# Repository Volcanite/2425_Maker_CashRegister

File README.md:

# 2425_Maker_CashRegister
Caisse enregistreuse à destination de la KFET. Elle permettrai de payer ses consommations et d'en avoir une traçabilité. On aurait également la possibilité de gérer les stocks et prévenir en cas de rupture. On pourrait également modifier les prix et les consommables proposés.

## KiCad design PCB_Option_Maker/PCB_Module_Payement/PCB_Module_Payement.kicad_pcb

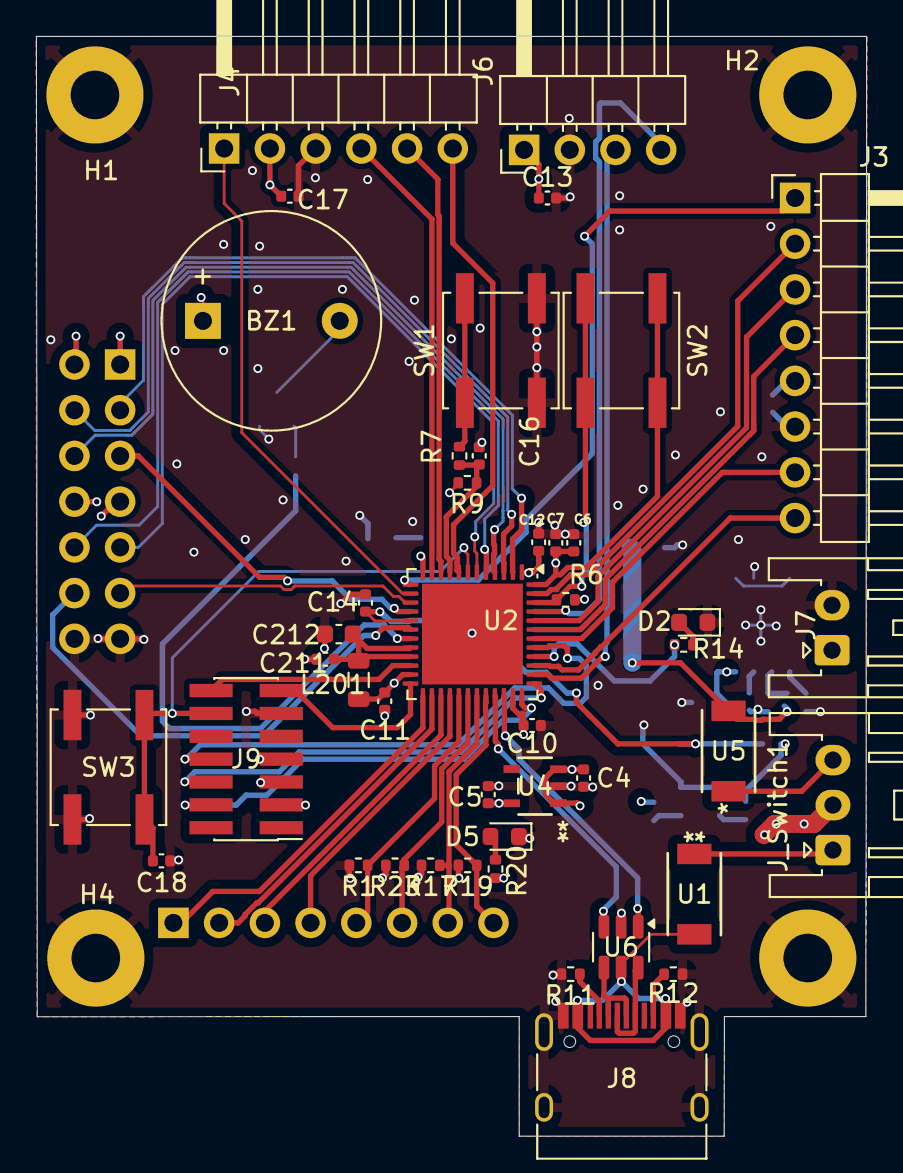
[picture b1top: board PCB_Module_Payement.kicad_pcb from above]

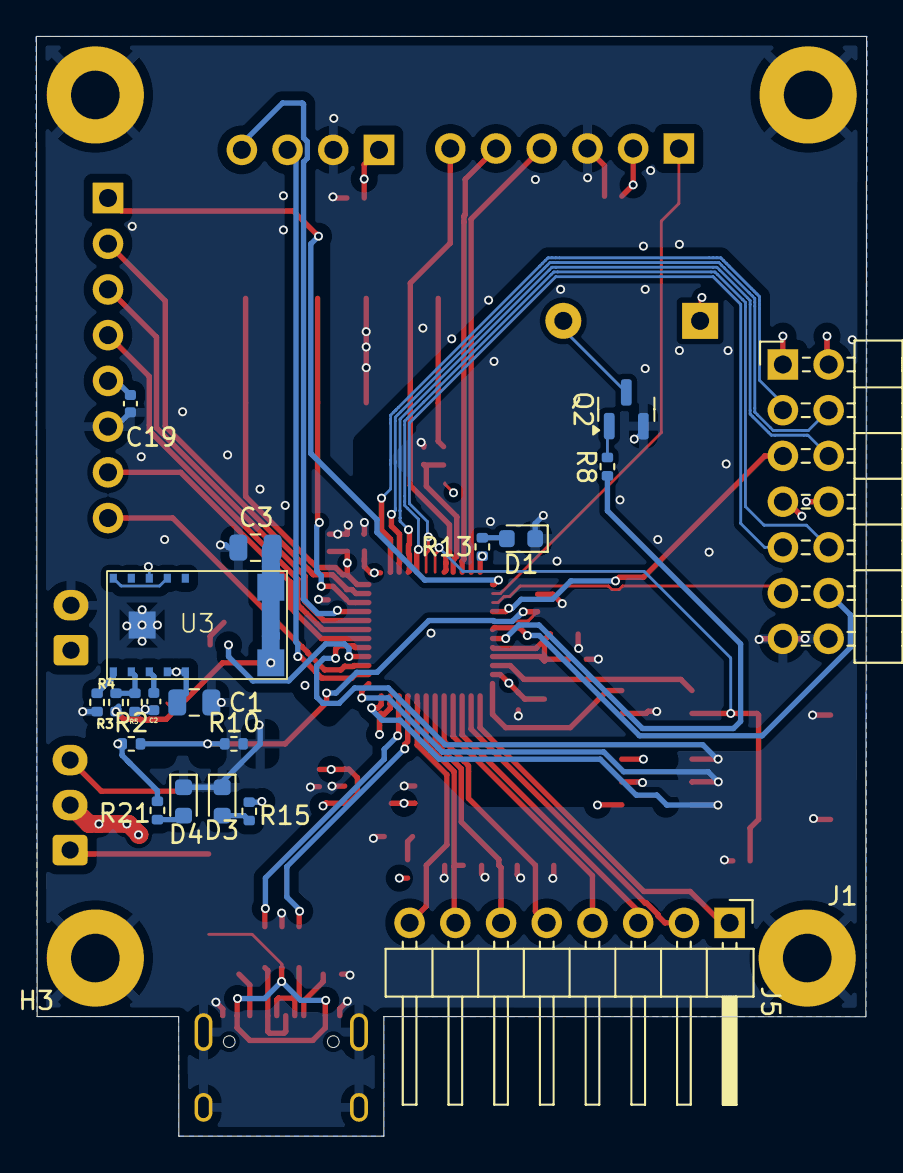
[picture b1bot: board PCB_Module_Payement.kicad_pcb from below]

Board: 4 copper layers, 46.1 x 61.1 mm, 68 parts (20 on the bottom side), 67 nets.

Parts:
BZ1: Buzzer; Buzzer_12x9.5RM7.6
C1: 10u; C_0805_2012Metric
C2, C4, C5, C13, C17, C19: 1u; C_0402_1005Metric
C3: 47u; C_0805_2012Metric
C6: 4u7; C_0402_1005Metric
C7, C10, C11, C12, C14, C16, C18, C211: 100n; C_0402_1005Metric
C212: 1u; C_0603_1608Metric
D1: LED Blue; LED_0603_1608Metric
D2: LED Amber; LED_0603_1608Metric
D3: LED Yellow; LED_0603_1608Metric
D4: LED_Blue; LED_0603_1608Metric
D5: LED_Green; LED_0603_1608Metric
H1, H2, H3, H4: MountingHole_Pad; MountingHole_2.7mm_M2.5_Pad
J1: Conn_02x07_Odd_Even; PinHeader_2x07_P2.54mm_Horizontal
J3, J5: Conn_01x08; PinHeader_1x08_P2.54mm_Horizontal
J4: Conn_01x06; PinHeader_1x06_P2.54mm_Horizontal
J6: Conn_01x04; PinHeader_1x04_P2.54mm_Horizontal
J7: Conn_01x02; JST_XA_S02B-XASK-1_1x02_P2.50mm_Horizontal
J8: USB_C_Receptacle_USB2.0; USB_C_Receptacle_HRO_TYPE-C-31-M-12
J9: Conn_ST_STDC14; PinHeader_2x07_P1.27mm_Vertical_SMD
J_Switch1: Conn_01x03; JST_XA_S03B-XASK-1_1x03_P2.50mm_Horizontal
L201: 39n; L_0805_2012Metric
Q2: MMBT2222A; SOT-23
R1, R17, R19, R23: 10K; R_0402_1005Metric
R2: 168K; R_0402_1005Metric
R3: 5k6; R_0402_1005Metric
R4: 49k9; R_0402_1005Metric
R5, R6, R7, R9: 10k; R_0402_1005Metric
R8: 1K; R_0402_1005Metric
R10: 68K; R_0402_1005Metric
R11, R12: 5.1K; R_0402_1005Metric
R13, R14, R15: 1k7; R_0402_1005Metric
R20: 510; R_0402_1005Metric
R21: R; R_0402_1005Metric
SW1, SW2, SW3: SW_Push; SW_Push_1P1T_NO_CK_KSC6xxJ
U1, U5: FSV330AF; DO-214AD_ONS
U2: STM32G431CBUx; QFN-48-1EP_7x7mm_P0.5mm_EP5.6x5.6mm
U3: 171013801; Wurth_171013801
U4: BU33SD5WG-TR; SSOP5_ROM
U6: USBLC6-2SC6; SOT-23-6

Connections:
5V_BUCK: C3.1, R4.1, U3.6 (Vout), U3.7 (Vout), U5.2 (A)
5V_USB: J8.A4 (VBUS), J8.A9 (VBUS), J8.B4 (VBUS), J8.B9 (VBUS), U1.2 (A), U6.5 (VBUS)
+3.3V: C5.2, C6.1, C7.1, C10.1, C11.1, C12.1, J1.7, J1.8, J9.3 (VCC), L201.1, R9.2, R20.1, SW2.2, U2.1 (VBAT), U2.23 (VDD), U2.35 (VDD), U2.48 (VDD), U4.5 (VOUT)
+3.3VA: C211.1, C212.1, L201.2, U2.20 (VREF+), U2.21 (VDDA)
+5V: BZ1.1 (+), C4.1, C13.1, C17.1, C19.1, J1.1, J1.2, J3.5, J4.2, J6.1, J_Switch1.2, R15.1, U4.1 (VIN), U4.3 (STBY)
/Alim/Charge_Batterie: C14.1, R2.2, R10.1, U2.17 (PB0)
/Modules/Bt_RXD: J4.5, U2.10 (PA2)
/Modules/Bt_TXD: J4.4, U2.11 (PA3)
/Modules/Culomn1: J5.5, R1.1, U2.29 (PC6)
/Modules/Culomn2: J5.6, R23.1, U2.30 (PA8)
/Modules/Culomn3: J5.7, R17.1, U2.31 (PA9)
/Modules/Culomn4: J5.8, R19.1, U2.32 (PA10)
/Modules/I2C1_SCL: J6.4, U2.45 (PB7)
/Modules/I2C1_SDA: J6.3, U2.38 (PA15)
/Modules/IRQ: J3.8, U2.39 (PC10)
/Modules/KEY: J4.6, U2.8 (PA0)
/Modules/R0W1: J5.1, U2.25 (PB12)
/Modules/ROW2: J5.2, U2.26 (PB13)
/Modules/ROW3: J5.3, U2.27 (PB14)
/Modules/ROW4: J5.4, U2.28 (PB15)
/Modules/RSTO: J3.2, U2.47 (PB9)
/Modules/SPI1_Miso: J3.7, U2.42 (PB4)
/Modules/SPI1_Mosi: J3.4, U2.43 (PB5)
/Modules/SPI1_SCK: J3.1, U2.13 (PA5)
/Modules/SS: J3.3, U2.44 (PB6)
/Modules/STATE: J4.1, U2.14 (PA6)
/STM32/BL_LED: R13.1, U2.12 (PA4)
/STM32/BOOT0: R6.1, SW2.1, U2.46 (PB8)
/STM32/BUZZER: R8.1, U2.19 (PB2)
/STM32/Bt_Button: C16.1, R7.2, R9.1, U2.9 (PA1)
/STM32/D+: J8.A6 (D+), J8.B6 (D+), U6.6 (I/O1)
/STM32/D-: J8.A7 (D-), J8.B7 (D-), U6.4 (I/O2)
/STM32/NRST: C18.2, J9.12 (~RST), SW3.2, U2.7 (PG10)
/STM32/PA7: J1.11, U2.15 (PA7)
/STM32/PC4: J1.5, U2.16 (PC4)
/STM32/PC13: J1.3, U2.2 (PC13)
/STM32/PC14: J1.4, U2.3 (PC14)
/STM32/PC15: J1.6, U2.4 (PC15)
/STM32/PF0: J1.10, U2.5 (PF0)
/STM32/PF1: J1.9, U2.6 (PF1)
/STM32/Pb1: J1.12, U2.18 (PB1)
/STM32/RFID_LED: R14.1, U2.40 (PC11)
/STM32/SWCLK: J9.6 (JCLK/SWCLK), U2.37 (PA14)
/STM32/SWDIO: J9.4 (JTMS/SWDIO), U2.36 (PA13)
/STM32/SWO: J9.8 (JTDO/SWO), U2.41 (PB3)
/STM32/USART3_RX: J9.14 (VCP_TX), U2.22 (PB10)
/STM32/USART3_TX: J9.13 (VCP_RX), U2.24 (PB11)
/STM32/USB_D+: U2.34 (PA12), U6.1 (I/O1)
/STM32/USB_D-: U2.33 (PA11), U6.3 (I/O2)
GND: C1.2, C2.2, C3.2, C4.2, C5.1, C6.2, C7.2, C10.2, C11.2, C12.2, C13.2, C14.2, C16.2, C17.2, C18.1, C19.2, C211.2, C212.2, D1.1 (K), D2.1 (K), D3.1 (K), D4.1 (K), D5.1 (K), H1.1, H2.1, H3.1, H4.1, J1.13, J1.14, J3.6, J4.3, J6.2, J7.2, J8.A1 (GND), J8.A12 (GND), J8.B1 (GND), J8.B12 (GND), J8.S1 (SHIELD), J9.5 (GND), J9.7 (GND), J9.11 (GNDDetect), Q2.2 (E), R1.2, R3.2, R5.2, R6.2, R10.2, R11.2, R12.2, R17.2, R19.2, R23.2, SW1.1, SW3.1, U2.49 (VSS), U3.10 (AGND), U3.13 (PGND), U4.2 (GND), U6.2 (GND)
unnamed: BZ1.2 (-), Q2.3 (C)
unnamed: D1.2 (A), R13.2
unnamed: D2.2 (A), R14.2
unnamed: D3.2 (A), R15.2
unnamed: D4.2 (A), R21.2
unnamed: D5.2 (A), R20.2
unnamed: J8.A5 (CC1), R11.1
unnamed: J8.B5 (CC2), R12.1
unnamed: J_Switch1.1, U1.1 (K)
unnamed: J_Switch1.3, U5.1 (K)
unnamed: Q2.1 (B), R8.2
unnamed: R7.1, SW1.2
unnamed: U3.9 (VIN), U3.12 (EN)
unnamed: R4.2, R5.1, U3.2 (FB)
unnamed: R3.1, U3.1 (FSW_1)
unnamed: C2.1, U3.3 (Vcc)
VCC: C1.1, J7.1, R2.1, R21.1, U3.4 (Vin), U3.5 (Vin)

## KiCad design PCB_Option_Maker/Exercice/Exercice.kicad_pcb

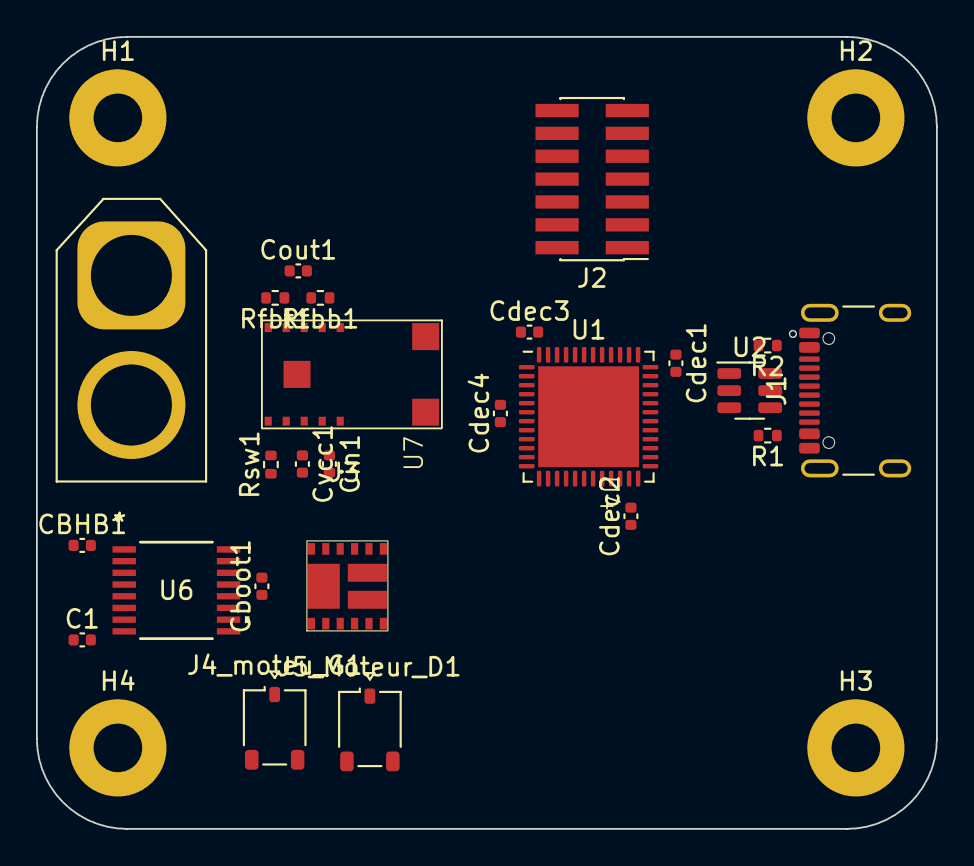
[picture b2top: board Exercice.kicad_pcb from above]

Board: 4 copper layers, 50.0 x 44.0 mm, 29 parts (0 on the bottom side), 28 nets, no tracks yet.

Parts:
C1: 0.2u; C_0402_1005Metric
CBHB1: 0.2u; C_0402_1005Metric
Cboot1: 2u; C_0402_1005Metric
Cdec1: 4u7; C_0402_1005Metric
Cdec2, Cdec3, Cdec4: 100n; C_0402_1005Metric
Cin1: 10u; C_0402_1005Metric
Cout1: 47u; C_0402_1005Metric
Cvcc1: 1u; C_0402_1005Metric
H1, H2, H3, H4: MountingHole_Pad; MountingHole_2.7mm_M2.5_Pad
J1: USB_C_Receptacle_USB2.0_16P; USB_C_Receptacle_GCT_USB4105-xx-A_16P_TopMnt_Horizontal
J2: Conn_02x07_Odd_Even; PinHeader_2x07_P1.27mm_Vertical_SMD
J3: Conn_01x02; AMASS_XT60-F_1x02_P7.20mm_Vertical
J4_moteu_G1, J5_Moteur_D1: Conn_01x01; JST_ACH_BM01B-ACHSS-A-GAN-ETF_1x01-1MP_P1.20mm_Vertical
R1, R2: 5.1K; R_0402_1005Metric
Rfbb1: 137K; R_0402_1005Metric
Rfbt1: 402K; R_0402_1005Metric
Rsw1: 5.6K; R_0402_1005Metric
U1: STM32G431CBUx; QFN-48-1EP_7x7mm_P0.5mm_EP5.6x5.6mm
U2: USBLC6-2SC6; SOT-23-6
U4: Wurth_171013801
U6: MIC4606-2YTS-TR; TSSOP16_TS_MCH_MIS
U7: NMOS_FDMQ86530L

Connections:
/AHO: U6.9 (AHO), U7.12 (G4)
/ALO: U6.11 (ALO), U7.9 (G3)
/APWM: U1.13 (PA5), U6.6 (APWM)
/BHO: U6.16 (BHO), U7.1 (G1)
/BLO: U6.14 (BLO), U7.4 (G2)
/BPWM: U1.14 (PA6), U6.3 (BPWM)
/D+: J1.A6 (D+), J1.B6 (D+), U2.6 (I/O1)
/D-: J1.A7 (D-), J1.B7 (D-), U2.4 (I/O2)
/GND: Cin1.2, Cout1.2, Cvcc1.2, Rfbb1.1, Rsw1.1, U4.10 (AGND), U4.13 (PGND)
/NRST: Cdec4.1, J2.12, U1.7 (PG10)
/SWDCK: J2.6, U1.37 (PA14)
/SWDIO: J2.4, U1.36 (PA13)
/USB_DM: U1.33 (PA11), U2.3 (I/O2)
/USB_DP: U1.34 (PA12), U2.1 (I/O1)
/Usart2_Rx: J2.13, U1.11 (PA3)
/Usart2_Tx: J2.14, U1.10 (PA2)
/V_USB: J1.A4 (VBUS), J1.A9 (VBUS), J1.B4 (VBUS), J1.B9 (VBUS), U2.5 (VBUS)
/Vout_3V3: Cdec1.2, Cdec2.2, Cdec3.2, Cout1.1, J2.3, Rfbt1.2, U1.1 (VBAT), U1.20 (VREF+), U1.21 (VDDA), U1.23 (VDD), U1.35 (VDD), U1.48 (VDD), U4.6 (Vout), U4.7 (Vout)
ISO_GND: C1.1, CBHB1.1, Cboot1.2, Cdec1.1, Cdec2.1, Cdec3.1, Cdec4.2, H1.1, H2.1, H3.1, H4.1, J1.A1 (GND), J1.A12 (GND), J1.B1 (GND), J1.B12 (GND), J1.S1 (SHIELD), J2.5, J2.7, J2.11, J3.1, J4_moteu_G1.1, J5_Moteur_D1.1, R1.2, R2.2, U1.49 (VSS), U2.2 (GND), U6.10 (AHS), U6.15 (BHS), U7.3 (S1/D2), U7.5 (S2), U7.6 (S2), U7.7 (S3), U7.8 (S3), U7.10 (D3/S4)
unnamed: J1.A5 (CC1), R1.1
unnamed: J1.B5 (CC2), R2.1
unnamed: U4.9 (VIN), U4.12 (EN)
unnamed: Rfbb1.2, Rfbt1.1, U4.2 (FB)
unnamed: Rsw1.2, U4.1 (FSW_1)
unnamed: Cvcc1.1, U4.3 (Vcc)
unnamed: C1.2, U6.8 (AHB)
unnamed: CBHB1.2, U6.1 (BHB)
Vin_15V: Cboot1.1, Cin1.1, J3.2, U4.4 (Vin), U4.5 (Vin), U6.2 (EN), U6.12 (VDD), U7.2 (D1/D4), U7.11 (D1/D4)

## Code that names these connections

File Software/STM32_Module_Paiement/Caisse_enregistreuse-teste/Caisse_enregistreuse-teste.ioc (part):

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Mcu.Name=STM32L476R(C-E-G)Tx
Mcu.Package=LQFP64
Mcu.UserName=STM32L476RGTx
PA0.Signal=S_TIM2_CH1
PA10.GPIOParameters=GPIO_PuPd,GPIO_Label
PA10.GPIO_Label=Col4
PA10.GPIO_PuPd=GPIO_PULLDOWN
PA10.Signal=GPIO_Output
PA13\ (JTMS-SWDIO).GPIOParameters=GPIO_Label
PA13\ (JTMS-SWDIO).GPIO_Label=TMS
PA13\ (JTMS-SWDIO).Mode=Serial_Wire
PA13\ (JTMS-SWDIO).Signal=SYS_JTMS-SWDIO
PA14\ (JTCK-SWCLK).GPIOParameters=GPIO_Label
PA14\ (JTCK-SWCLK).GPIO_Label=TCK
PA14\ (JTCK-SWCLK).Mode=Serial_Wire
PA14\ (JTCK-SWCLK).Signal=SYS_JTCK-SWCLK
PA15\ (JTDI).GPIOParameters=GPIO_Speed,PinState,GPIO_PuPd,GPIO_Label
PA15\ (JTDI).GPIO_Label=nCS
PA15\ (JTDI).GPIO_PuPd=GPIO_NOPULL
PA15\ (JTDI).GPIO_Speed=GPIO_SPEED_FREQ_HIGH
PA15\ (JTDI).PinState=GPIO_PIN_SET
PA15\ (JTDI).Signal=GPIO_Output
PA2.GPIOParameters=GPIO_Speed,GPIO_PuPd,GPIO_Label,GPIO_Mode
PA2.GPIO_Label=USART_TX
PA2.GPIO_Mode=GPIO_MODE_AF_PP
PA2.GPIO_PuPd=GPIO_NOPULL
PA2.GPIO_Speed=GPIO_SPEED_FREQ_VERY_HIGH
PA2.Mode=Asynchronous
PA2.Signal=USART2_TX
PA3.GPIOParameters=GPIO_Speed,GPIO_PuPd,GPIO_Label,GPIO_Mode
PA3.GPIO_Label=USART_RX
PA3.GPIO_Mode=GPIO_MODE_AF_PP
PA3.GPIO_PuPd=GPIO_NOPULL
PA3.GPIO_Speed=GPIO_SPEED_FREQ_VERY_HIGH
PA3.Mode=Asynchronous
PA3.Signal=USART2_RX
PA5.GPIOParameters=GPIO_Speed,GPIO_PuPd,GPIO_Label,GPIO_ModeDefaultOutputPP
PA5.GPIO_Label=green
PA5.GPIO_ModeDefaultOutputPP=GPIO_MODE_OUTPUT_PP
PA5.GPIO_PuPd=GPIO_NOPULL
PA5.GPIO_Speed=GPIO_SPEED_FREQ_LOW
PA5.Signal=GPIO_Output
PA8.GPIOParameters=GPIO_PuPd,GPIO_Label
PA8.GPIO_Label=Row3
PA8.GPIO_PuPd=GPIO_PULLDOWN
PA8.Signal=GPIO_Input
PA9.GPIOParameters=GPIO_PuPd,GPIO_Label
PA9.GPIO_Label=Row2
PA9.GPIO_PuPd=GPIO_PULLDOWN
PA9.Signal=GPIO_Input
PB0.GPIOParameters=GPIO_PuPd,GPIO_Label
PB0.GPIO_Label=PN532_RST
PB0.GPIO_PuPd=GPIO_PULLUP
PB0.Signal=GPIO_Output
PB1.GPIOParameters=GPIO_PuPd,GPIO_Label
PB1.GPIO_Label=PN532_REQ
PB1.GPIO_PuPd=GPIO_PULLUP
PB1.Signal=GPIO_Output
PB10.GPIOParameters=GPIO_PuPd,GPIO_Label
PB10.GPIO_Label=Row4
PB10.GPIO_PuPd=GPIO_PULLDOWN
PB10.Signal=GPIO_Input
PB13.Mode=I2C
PB13.Signal=I2C2_SCL
PB14.Mode=I2C
PB14.Signal=I2C2_SDA
PB3\ (JTDO-TRACESWO).GPIOParameters=GPIO_PuPd,GPIO_Label
PB3\ (JTDO-TRACESWO).GPIO_Label=Col3
PB3\ (JTDO-TRACESWO).GPIO_PuPd=GPIO_PULLDOWN
PB3\ (JTDO-TRACESWO).Signal=GPIO_Output
PB4\ (NJTRST).GPIOParameters=GPIO_PuPd,GPIO_Label
PB4\ (NJTRST).GPIO_Label=Col1
PB4\ (NJTRST).GPIO_PuPd=GPIO_PULLDOWN
PB4\ (NJTRST).Signal=GPIO_Output
PB5.GPIOParameters=GPIO_PuPd,GPIO_Label
PB5.GPIO_Label=Col2
PB5.GPIO_PuPd=GPIO_PULLDOWN
PB5.Signal=GPIO_Output
PB6.Mode=I2C
PB6.Signal=I2C1_SCL
PB7.GPIOParameters=GPIO_Speed,GPIO_Label
PB7.GPIO_Label=RESET
PB7.GPIO_Speed=GPIO_SPEED_FREQ_HIGH
PB7.Signal=GPIO_Output
PB9.Mode=I2C
PB9.Signal=I2C1_SDA
PC1.Signal=ADCx_IN2
PC10.GPIOParameters=GPIO_PuPd,GPIO_Label
PC10.GPIO_Label=IRQ
PC10.GPIO_PuPd=GPIO_PULLUP
PC10.Signal=GPIO_Input
PC12.GPIOParameters=GPIO_Label
PC12.GPIO_Label=TX_BT_RX
PC12.Mode=Asynchronous
PC12.Signal=UART5_TX
PC13.GPIOParameters=GPIO_PuPd,GPIO_Label,GPIO_ModeDefaultEXTI
PC13.GPIO_Label=B1 [Blue PushButton]
PC13.GPIO_ModeDefaultEXTI=GPIO_MODE_IT_FALLING
PC13.GPIO_PuPd=GPIO_PULLUP
PC13.Signal=GPXTI13
PC14-OSC32_IN\ (PC14).Mode=LSE-External-Oscillator
PC14-OSC32_IN\ (PC14).Signal=RCC_OSC32_IN
PC15-OSC32_OUT\ (PC15).Mode=LSE-External-Oscillator
PC15-OSC32_OUT\ (PC15).Signal=RCC_OSC32_OUT
PC7.GPIOParameters=GPIO_PuPd,GPIO_Label
PC7.GPIO_Label=Row1
PC7.GPIO_PuPd=GPIO_PULLDOWN
PC7.Signal=GPIO_Input
PD2.GPIOParameters=GPIO_Label
PD2.GPIO_Label=RX_BT_TX
PD2.Mode=Asynchronous
PD2.Signal=UART5_RX
PH0-OSC_IN\ (PH0).Mode=HSE-External-Oscillator
PH0-OSC_IN\ (PH0).Signal=RCC_OSC_IN
PH1-OSC_OUT\ (PH1).Mode=HSE-External-Oscillator
PH1-OSC_OUT\ (PH1).Signal=RCC_OSC_OUT
RCC.HSE_VALUE=8000000
RCC.SYSCLKFreq_VALUE=80000000
RCC.SYSCLKSource=RCC_SYSCLKSOURCE_PLLCLK
board=NUCLEO-L476RG
boardIOC=true

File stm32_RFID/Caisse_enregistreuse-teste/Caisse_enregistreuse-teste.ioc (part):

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Mcu.Name=STM32L476R(C-E-G)Tx
Mcu.Package=LQFP64
Mcu.UserName=STM32L476RGTx
PA0.Signal=S_TIM2_CH1
PA13\ (JTMS-SWDIO).GPIOParameters=GPIO_Label
PA13\ (JTMS-SWDIO).GPIO_Label=TMS
PA13\ (JTMS-SWDIO).Mode=Serial_Wire
PA13\ (JTMS-SWDIO).Signal=SYS_JTMS-SWDIO
PA14\ (JTCK-SWCLK).GPIOParameters=GPIO_Label
PA14\ (JTCK-SWCLK).GPIO_Label=TCK
PA14\ (JTCK-SWCLK).Mode=Serial_Wire
PA14\ (JTCK-SWCLK).Signal=SYS_JTCK-SWCLK
PA15\ (JTDI).GPIOParameters=GPIO_Speed,GPIO_PuPd
PA15\ (JTDI).GPIO_PuPd=GPIO_NOPULL
PA15\ (JTDI).GPIO_Speed=GPIO_SPEED_FREQ_HIGH
PA15\ (JTDI).Signal=GPIO_Output
PA2.GPIOParameters=GPIO_Speed,GPIO_PuPd,GPIO_Label,GPIO_Mode
PA2.GPIO_Label=USART_TX
PA2.GPIO_Mode=GPIO_MODE_AF_PP
PA2.GPIO_PuPd=GPIO_NOPULL
PA2.GPIO_Speed=GPIO_SPEED_FREQ_VERY_HIGH
PA2.Mode=Asynchronous
PA2.Signal=USART2_TX
PA3.GPIOParameters=GPIO_Speed,GPIO_PuPd,GPIO_Label,GPIO_Mode
PA3.GPIO_Label=USART_RX
PA3.GPIO_Mode=GPIO_MODE_AF_PP
PA3.GPIO_PuPd=GPIO_NOPULL
PA3.GPIO_Speed=GPIO_SPEED_FREQ_VERY_HIGH
PA3.Mode=Asynchronous
PA3.Signal=USART2_RX
PA5.GPIOParameters=GPIO_Speed,GPIO_PuPd,GPIO_Label,GPIO_ModeDefaultOutputPP
PA5.GPIO_Label=green
PA5.GPIO_ModeDefaultOutputPP=GPIO_MODE_OUTPUT_PP
PA5.GPIO_PuPd=GPIO_NOPULL
PA5.GPIO_Speed=GPIO_SPEED_FREQ_LOW
PA5.Signal=GPIO_Output
PA8.Signal=GPIO_Output
PA9.Signal=GPIO_Output
PB10.Mode=Full_Duplex_Master
PB10.Signal=SPI2_SCK
PB14.GPIOParameters=GPIO_PuPd,GPIO_ModeDefaultEXTI
PB14.GPIO_ModeDefaultEXTI=GPIO_MODE_IT_FALLING
PB14.GPIO_PuPd=GPIO_PULLUP
PB14.Signal=GPXTI14
PB15.GPIOParameters=GPIO_PuPd,GPIO_ModeDefaultEXTI
PB15.GPIO_ModeDefaultEXTI=GPIO_MODE_IT_FALLING
PB15.GPIO_PuPd=GPIO_PULLUP
PB15.Signal=GPXTI15
PB7.GPIOParameters=GPIO_Speed
PB7.GPIO_Speed=GPIO_SPEED_FREQ_HIGH
PB7.Signal=GPIO_Output
PC10.GPIOParameters=GPIO_PuPd
PC10.GPIO_PuPd=GPIO_PULLUP
PC10.Signal=GPIO_Input
PC13.GPIOParameters=GPIO_PuPd,GPIO_Label,GPIO_ModeDefaultEXTI
PC13.GPIO_Label=B1 [Blue PushButton]
PC13.GPIO_ModeDefaultEXTI=GPIO_MODE_IT_FALLING
PC13.GPIO_PuPd=GPIO_PULLUP
PC13.Signal=GPXTI13
PC14-OSC32_IN\ (PC14).Mode=LSE-External-Oscillator
PC14-OSC32_IN\ (PC14).Signal=RCC_OSC32_IN
PC15-OSC32_OUT\ (PC15).Mode=LSE-External-Oscillator
PC15-OSC32_OUT\ (PC15).Signal=RCC_OSC32_OUT
PC2.Mode=Full_Duplex_Master
PC2.Signal=SPI2_MISO
PC3.Mode=Full_Duplex_Master
PC3.Signal=SPI2_MOSI
PC6.GPIOParameters=GPIO_PuPd,GPIO_ModeDefaultEXTI
PC6.GPIO_ModeDefaultEXTI=GPIO_MODE_IT_FALLING
PC6.GPIO_PuPd=GPIO_PULLUP
PC6.Signal=GPXTI6
PC7.GPIOParameters=GPIO_PuPd,GPIO_ModeDefaultEXTI
PC7.GPIO_ModeDefaultEXTI=GPIO_MODE_IT_FALLING
PC7.GPIO_PuPd=GPIO_PULLUP
PC7.Signal=GPXTI7
PC8.Signal=GPIO_Output
PC9.Signal=GPIO_Output
PH0-OSC_IN\ (PH0).Mode=HSE-External-Oscillator
PH0-OSC_IN\ (PH0).Signal=RCC_OSC_IN
PH1-OSC_OUT\ (PH1).Mode=HSE-External-Oscillator
PH1-OSC_OUT\ (PH1).Signal=RCC_OSC_OUT
RCC.HSE_VALUE=8000000
RCC.SYSCLKFreq_VALUE=64000000
RCC.SYSCLKSource=RCC_SYSCLKSOURCE_PLLCLK
board=NUCLEO-L476RG
boardIOC=true

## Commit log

2025-03-09 exo_pcb_push
2025-03-17 Create PCB_CashRegister
2025-03-17 add pcb
2025-03-17 update schematci
2025-03-20 pcb update
2025-03-22 update pcb
2025-03-31 stm32 test rfid
2026-02-12 Ajout interface Homme Machine
2026-02-12 Fichier indépendant bluetooth, rfid par I2C, écran
2026-02-12 Fichier indépendant bluetooth, rfid par I2C, écran (1)
2026-02-12 Fichier indépendant bluetooth, rfid par I2C, écran (2)
2026-02-13 Réorganisation Compte rendu projet
